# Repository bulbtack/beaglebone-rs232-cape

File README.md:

# BeagleBone RS-232 Cape #

A cape for the BeagleBone Black (and compatible derivatives) that adapts four of the onboard UARTs (UART1, UART2, UART4, and UART5) for use with RS-232 usage.
The cape also brings out UART0 from J1 to another FTDI compatible header.

## The Bill of Materials ##

Designator                              | Value                       | Size
----------------------------------------|-----------------------------|--------------
U1, U2                                  | ST232ECTR                   | TSSOP16 
C1, C2, C3, C4, C5, C6, C7, C8, C9, C10 | .1 uF X7R                   | 0402
P1, P2, P4, P5                          | Male Right Angle Header     | .1" 2x5
P3                                      | Female Socket               | .1" 1x6
P6                                      | Male Right Angle Header SMT | .1" 1x6
P8, P9                                  | Female Socket               | .1" 2x23

https://octopart.com/bom-tool/arnFMVWq

## License ##

This project is licesned under the CERN Open Hardware License 1.2.

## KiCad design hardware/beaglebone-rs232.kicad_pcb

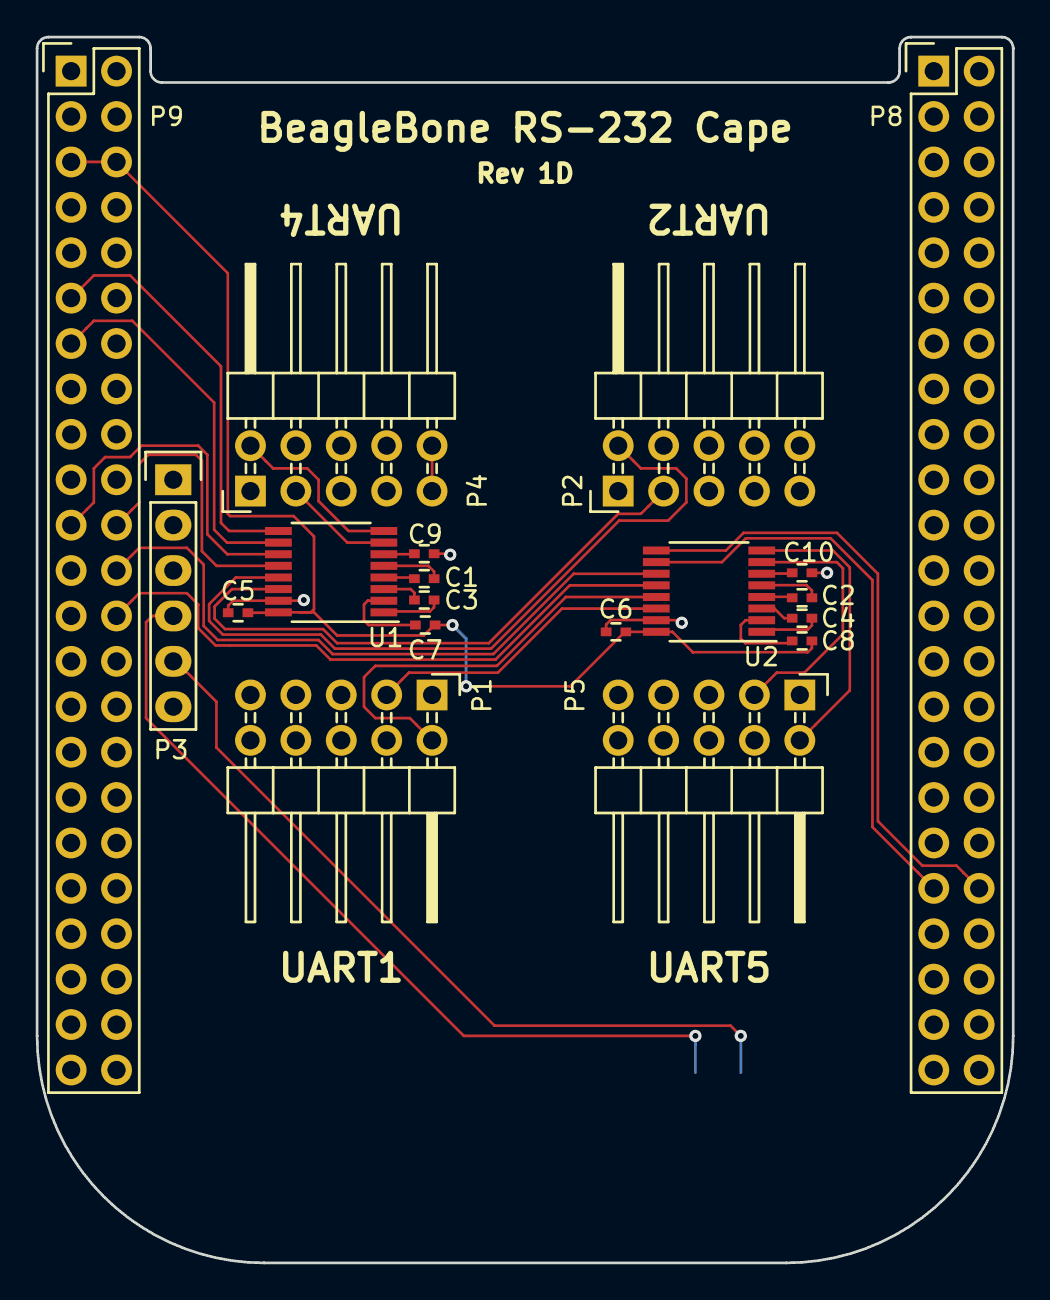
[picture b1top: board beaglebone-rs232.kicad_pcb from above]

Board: 2 copper layers, 54.6 x 68.6 mm, 20 parts (1 on the bottom side), 32 nets.

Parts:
C1, C2, C3, C4, C5, C6, C7, C8, C9, C10: .1uF; C_0402
P1, P2, P4, P5: CONN_02X05; Pin_Header_Angled_2x05
P3: CONN_01X06; Pin_Header_Straight_1x06
P6: CONN_01X06; Pin_Header_Angled_1x06_SMT
P8, P9: CONN_02X23; Pin_Header_Straight_2x23
U1, U2: ST232C; TSSOP-16_4.4x5mm_Pitch0.65mm

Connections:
+5VD: C5.1, C6.1, C7.1, C8.1, P9.5, P9.6, U1.16, U2.16
/C1_MINUS_1: C3.2, U1.3
/C1_MINUS_2: C4.2, U2.3
/C1_PLUS_1: C3.1, U1.1
/C1_PLUS_2: C4.1, U2.1
/C2_MINUS_1: C1.2, U1.5
/C2_MINUS_2: C2.2, U2.5
/C2_PLUS_1: C1.1, U1.4
/C2_PLUS_2: C2.1, U2.4
/UART0_RXD: P3.4, P6.4
/UART0_TXD: P3.5, P6.5
/V_MINUS_1: C9.2, U1.6
/V_MINUS_2: C10.2, U2.6
/V_PLUS_1: C7.2, U1.2
/V_PLUS_2: C8.2, U2.2
GNDD: C5.2, C6.2, C9.1, C10.1, P1.5, P2.5, P3.1, P4.5, P5.5, P6.1, P8.1, P8.2, P9.1, P9.2, P9.43, P9.44, P9.45, P9.46, U1.15, U2.15
SER1_RX: P1.2, U2.13
SER1_TX: P1.3, U2.14
SER2_RX: P2.2, U1.13
SER2_TX: P2.3, U1.14
SER4_RX: P4.2, U1.8
SER4_TX: P4.3, U1.7
SER5_RX: P5.2, U2.8
SER5_TX: P5.3, U2.7
UART1_RXD: P9.26, U2.12
UART1_TXD: P9.24, U2.11
UART2_RXD: P9.22, U1.12
UART2_TXD: P9.21, U1.11
UART4_RXD: P9.11, U1.9
UART4_TXD: P9.13, U1.10
UART5_RXD: P8.38, U2.9
UART5_TXD: P8.37, U2.10

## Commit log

2016-11-17 Add files
2016-12-13 Fix swapped pins on Serial 1 Header, rev to version 1D
